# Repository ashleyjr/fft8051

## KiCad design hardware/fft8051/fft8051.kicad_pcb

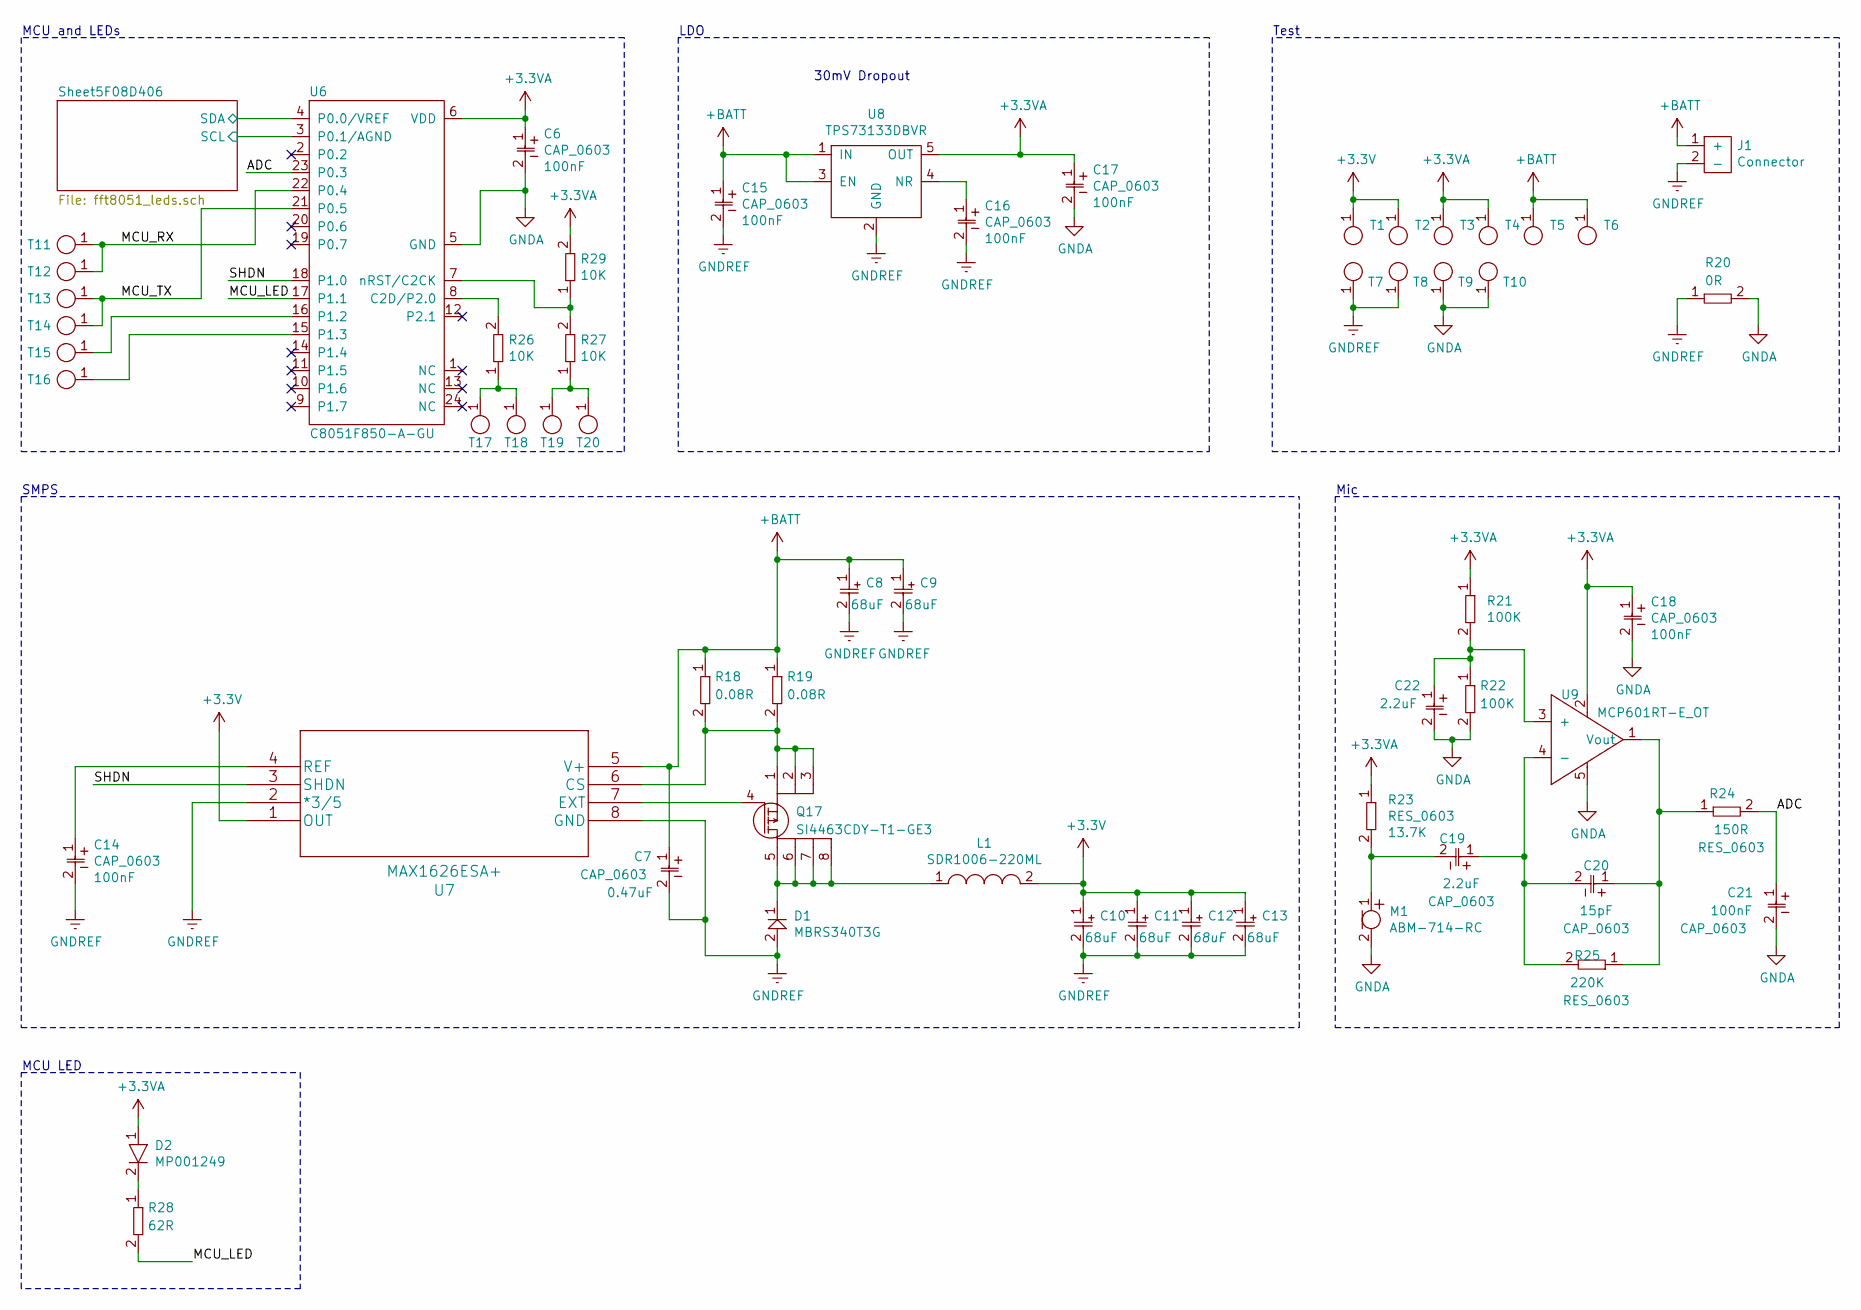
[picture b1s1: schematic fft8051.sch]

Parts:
C6, C7, C14, C15, C16, C17, C18, C19, C20, C21, C22: CAP_0603; 0603
C8, C9, C10, C11, C12, C13: T55B686M6R3C0070
D1: MBRS340T3G
D2: MP001249
J1: Connector
L1: SDR1006-220ML
M1: ABM-714-RC
Q17: SI4463CDY-T1-GE3
R18, R19, R20, R21, R22, R23, R24, R25, R26, R27, R28, R29: RES_0603; 0603
T1, T2, T3, T4, T5, T6, T7, T8, T9, T10, T11, T12, T13, T14, T15, T16, T17, T18, T19, T20: TestPoints; TestPoint
U6: C8051F850-A-GU
U7: MAX1626ESA+; MAX1626ESA&plus_
U8: TPS73133DBVR
U9: MCP601RT-E_OT; MCP601RT

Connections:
+3.3VA: C6.1, C17.1, C18.1, D2.1, R21.1, R23.1, R29.2, T3.1, T4.1, U6.6 (VDD), U8.5 (OUT), U9.2
+3V3: C10.1, C11.1, C12.1, C13.1, L1.2, T1.1, T2.1, U7.1 (OUT); also elsewhere on the board
+BATT: C7.1, C8.1, C9.1, C15.1, J1.1 (+), R18.1, R19.1, T5.1, T6.1, U7.5 (V+), U8.1 (IN), U8.3 (EN)
/ADC: C21.1, R24.2, U6.23 (P0.3)
/MCU_LED: R28.2, U6.17 (P1.1)
/MCU_RX: T11.1, T12.1, U6.22 (P0.4)
/MCU_TX: T13.1, T14.1, U6.21 (P0.5)
/SHDN: U6.18 (P1.0), U7.3 (SHDN)
/Sheet5F08D406/SCL: U6.3 (P0.1/AGND); also elsewhere on the board
/Sheet5F08D406/SDA: U6.4 (P0.0/VREF); also elsewhere on the board
GNDA: C6.2, C17.2, C18.2, C21.2, C22.2, M1.2, R20.2, R22.2, T9.1, T10.1, U6.5 (GND), U9.5
GNDREF: C7.2, C8.2, C9.2, C10.2, C11.2, C12.2, C13.2, C14.2, C15.2, C16.2, D1.2, J1.2 (-), R20.1, T7.1, T8.1, U7.2 (*3/5), U7.8 (GND), U8.2 (GND); also elsewhere on the board
unnamed: C14.1, U7.4 (REF)
unnamed: C16.1, U8.4 (NR)
unnamed: C19.1, C20.2, R25.2, U9.4 (-)
unnamed: C19.2, M1.1, R23.2
unnamed: C20.1, R24.1, R25.1, U9.1 (Vout)
unnamed: C22.1, R21.2, R22.1, U9.3 (+)
unnamed: D1.1, L1.1, Q17.5, Q17.6, Q17.7, Q17.8
unnamed: D2.2, R28.1
unnamed: Q17.1, Q17.2, Q17.3, R18.2, R19.2, U7.6 (CS)
unnamed: Q17.4, U7.7 (EXT)
unnamed: R26.1, T17.1, T18.1
unnamed: R26.2, U6.8 (C2D/P2.0)
unnamed: R27.1, T19.1, T20.1
unnamed: R27.2, R29.1, U6.7 (nRST/C2CK)
unnamed: T15.1, U6.16 (P1.2)
unnamed: T16.1, U6.15 (P1.3)

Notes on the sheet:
SMPS
MCU and LEDs
LDO
30mV Dropout
Test
Mic
MCU LED

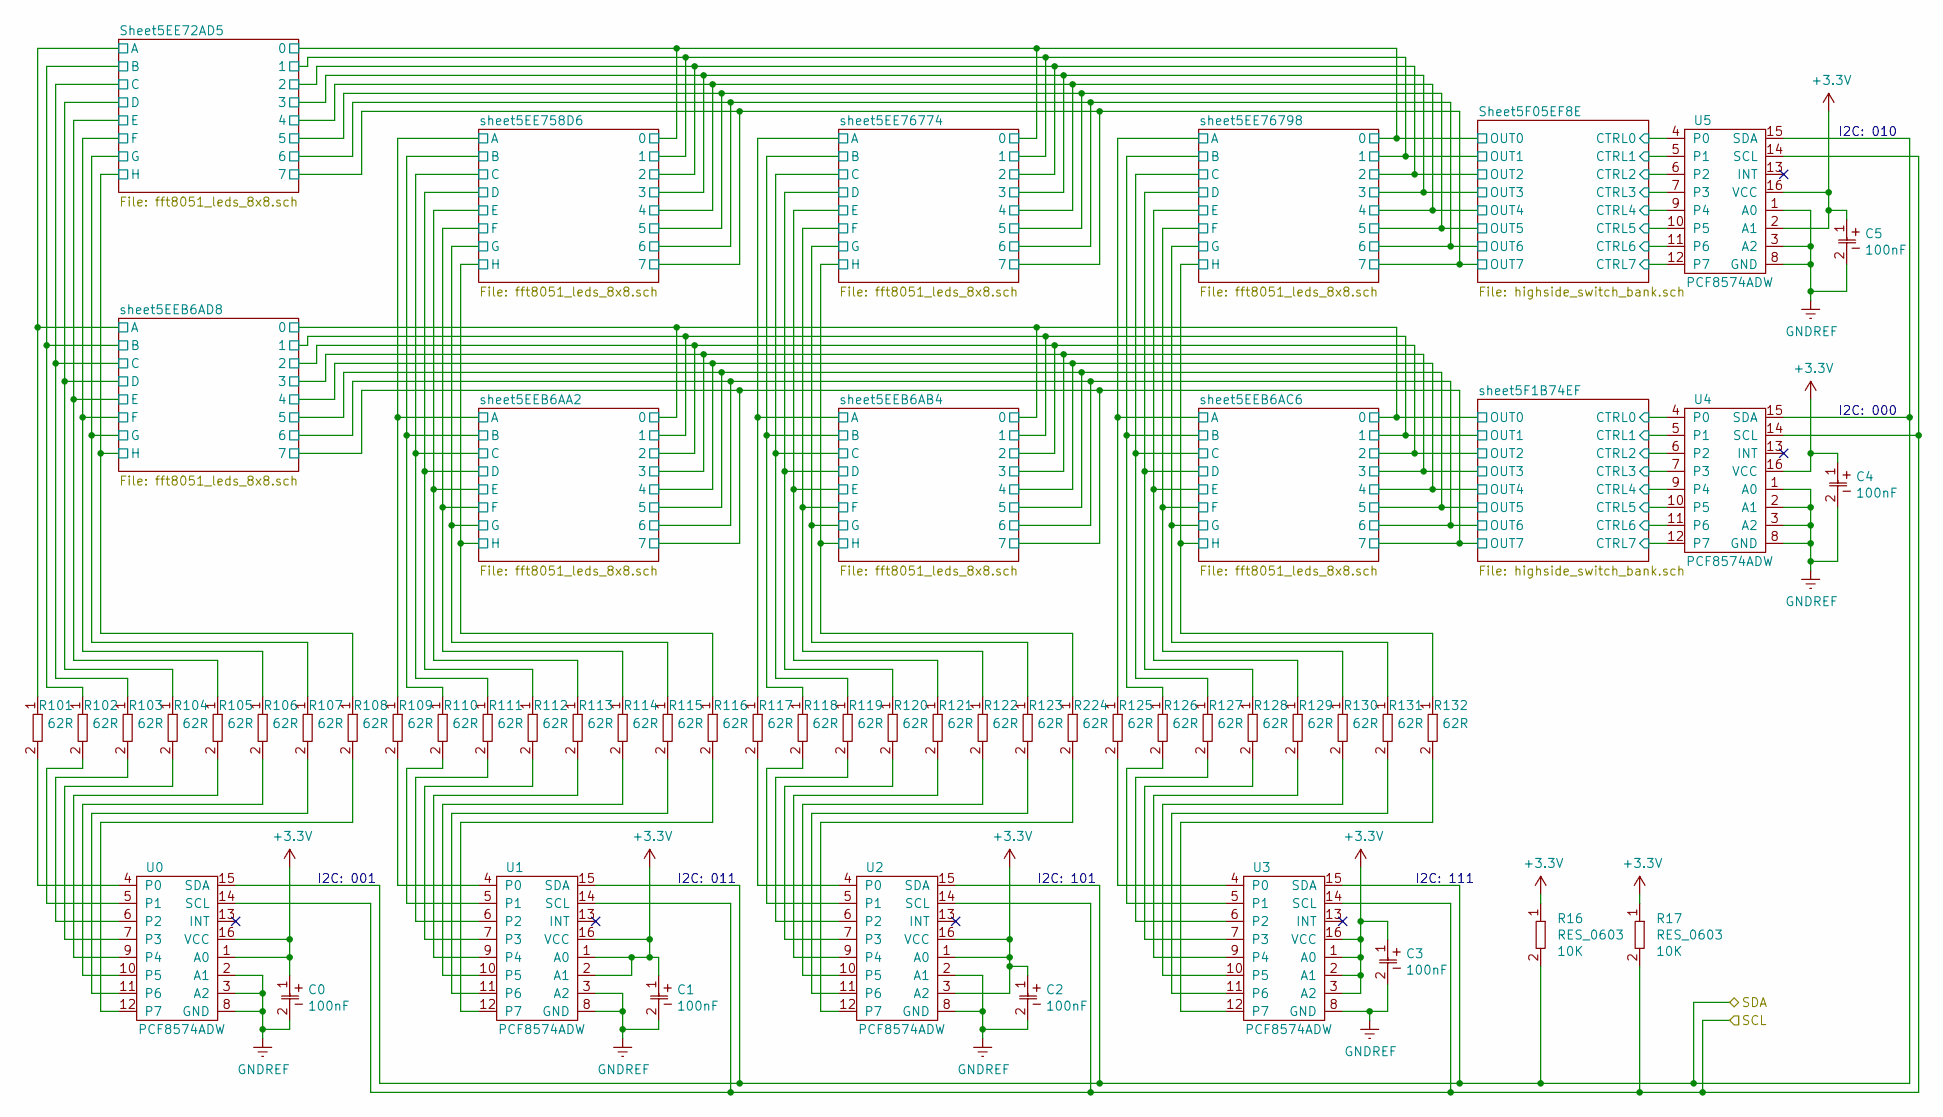
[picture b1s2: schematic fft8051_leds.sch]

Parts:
C0, C1, C2, C3, C4, C5: CAP_0603; 0603
R16, R17, R101, R102, R103, R104, R105, R106, R107, R108, R109, R110, R111, R112, R113, R114, R115, R116, R117, R118, R119, R120, R121, R122, R123, R125, R126, R127, R128, R129, R130, R131, R132, R224: RES_0603; 0603
U0, U1, U2, U3, U4, U5: PCF8574ADW

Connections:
+3V3: C0.1, C1.1, C2.1, C3.1, C4.1, C5.1, R16.1, R17.1, U0.1 (A0), U0.16 (VCC), U1.1 (A0), U1.2 (A1), U1.16 (VCC), U2.1 (A0), U2.3 (A2), U2.16 (VCC), U3.1 (A0), U3.2 (A1), U3.3 (A2), U3.16 (VCC), U4.16 (VCC), U5.2 (A1), U5.16 (VCC); also elsewhere on the board
/Sheet5F08D406/SCL: R17.2, U0.14 (SCL), U1.14 (SCL), U2.14 (SCL), U3.14 (SCL), U4.14 (SCL), U5.14 (SCL); also elsewhere on the board
/Sheet5F08D406/SDA: R16.2, U0.15 (SDA), U1.15 (SDA), U2.15 (SDA), U3.15 (SDA), U4.15 (SDA), U5.15 (SDA); also elsewhere on the board
/Sheet5F08D406/Sheet5EE72AD5/A: R101.1; also elsewhere on the board
/Sheet5F08D406/Sheet5EE72AD5/B: R102.1; also elsewhere on the board
/Sheet5F08D406/Sheet5EE72AD5/C: R103.1; also elsewhere on the board
/Sheet5F08D406/Sheet5EE72AD5/D: R104.1; also elsewhere on the board
/Sheet5F08D406/Sheet5EE72AD5/E: R105.1; also elsewhere on the board
/Sheet5F08D406/Sheet5EE72AD5/F: R106.1; also elsewhere on the board
/Sheet5F08D406/Sheet5EE72AD5/G: R107.1; also elsewhere on the board
/Sheet5F08D406/Sheet5EE72AD5/H: R108.1; also elsewhere on the board
/Sheet5F08D406/Sheet5F05EF8E/CTRL0: U5.4 (P0); also elsewhere on the board
/Sheet5F08D406/Sheet5F05EF8E/CTRL1: U5.5 (P1); also elsewhere on the board
/Sheet5F08D406/Sheet5F05EF8E/CTRL2: U5.6 (P2); also elsewhere on the board
/Sheet5F08D406/Sheet5F05EF8E/CTRL3: U5.7 (P3); also elsewhere on the board
/Sheet5F08D406/Sheet5F05EF8E/CTRL4: U5.9 (P4); also elsewhere on the board
/Sheet5F08D406/Sheet5F05EF8E/CTRL5: U5.10 (P5); also elsewhere on the board
/Sheet5F08D406/Sheet5F05EF8E/CTRL6: U5.11 (P6); also elsewhere on the board
/Sheet5F08D406/Sheet5F05EF8E/CTRL7: U5.12 (P7); also elsewhere on the board
/Sheet5F08D406/sheet5EE758D6/A: R109.1; also elsewhere on the board
/Sheet5F08D406/sheet5EE758D6/B: R110.1; also elsewhere on the board
/Sheet5F08D406/sheet5EE758D6/C: R111.1; also elsewhere on the board
/Sheet5F08D406/sheet5EE758D6/D: R112.1; also elsewhere on the board
/Sheet5F08D406/sheet5EE758D6/E: R113.1; also elsewhere on the board
/Sheet5F08D406/sheet5EE758D6/F: R114.1; also elsewhere on the board
/Sheet5F08D406/sheet5EE758D6/G: R115.1; also elsewhere on the board
/Sheet5F08D406/sheet5EE758D6/H: R116.1; also elsewhere on the board
/Sheet5F08D406/sheet5EE76774/A: R117.1; also elsewhere on the board
/Sheet5F08D406/sheet5EE76774/B: R118.1; also elsewhere on the board
/Sheet5F08D406/sheet5EE76774/C: R119.1; also elsewhere on the board
/Sheet5F08D406/sheet5EE76774/D: R120.1; also elsewhere on the board
/Sheet5F08D406/sheet5EE76774/E: R121.1; also elsewhere on the board
/Sheet5F08D406/sheet5EE76774/F: R122.1; also elsewhere on the board
/Sheet5F08D406/sheet5EE76774/G: R123.1; also elsewhere on the board
/Sheet5F08D406/sheet5EE76774/H: R224.1; also elsewhere on the board
/Sheet5F08D406/sheet5EE76798/A: R125.1; also elsewhere on the board
/Sheet5F08D406/sheet5EE76798/B: R126.1; also elsewhere on the board
/Sheet5F08D406/sheet5EE76798/C: R127.1; also elsewhere on the board
/Sheet5F08D406/sheet5EE76798/D: R128.1; also elsewhere on the board
/Sheet5F08D406/sheet5EE76798/E: R129.1; also elsewhere on the board
/Sheet5F08D406/sheet5EE76798/F: R130.1; also elsewhere on the board
/Sheet5F08D406/sheet5EE76798/G: R131.1; also elsewhere on the board
/Sheet5F08D406/sheet5EE76798/H: R132.1; also elsewhere on the board
/Sheet5F08D406/sheet5F1B74EF/CTRL0: U4.4 (P0); also elsewhere on the board
/Sheet5F08D406/sheet5F1B74EF/CTRL1: U4.5 (P1); also elsewhere on the board
/Sheet5F08D406/sheet5F1B74EF/CTRL2: U4.6 (P2); also elsewhere on the board
/Sheet5F08D406/sheet5F1B74EF/CTRL3: U4.7 (P3); also elsewhere on the board
/Sheet5F08D406/sheet5F1B74EF/CTRL4: U4.9 (P4); also elsewhere on the board
/Sheet5F08D406/sheet5F1B74EF/CTRL5: U4.10 (P5); also elsewhere on the board
/Sheet5F08D406/sheet5F1B74EF/CTRL6: U4.11 (P6); also elsewhere on the board
/Sheet5F08D406/sheet5F1B74EF/CTRL7: U4.12 (P7); also elsewhere on the board
GNDREF: C0.2, C1.2, C2.2, C3.2, C4.2, C5.2, U0.2 (A1), U0.3 (A2), U0.8 (GND), U1.3 (A2), U1.8 (GND), U2.2 (A1), U2.8 (GND), U3.8 (GND), U4.1 (A0), U4.2 (A1), U4.3 (A2), U4.8 (GND), U5.1 (A0), U5.3 (A2), U5.8 (GND); also elsewhere on the board
unnamed: R101.2, U0.4 (P0)
unnamed: R102.2, U0.5 (P1)
unnamed: R103.2, U0.6 (P2)
unnamed: R104.2, U0.7 (P3)
unnamed: R105.2, U0.9 (P4)
unnamed: R106.2, U0.10 (P5)
unnamed: R107.2, U0.11 (P6)
unnamed: R108.2, U0.12 (P7)
unnamed: R109.2, U1.4 (P0)
unnamed: R110.2, U1.5 (P1)
unnamed: R111.2, U1.6 (P2)
unnamed: R112.2, U1.7 (P3)
unnamed: R113.2, U1.9 (P4)
unnamed: R114.2, U1.10 (P5)
unnamed: R115.2, U1.11 (P6)
unnamed: R116.2, U1.12 (P7)
unnamed: R117.2, U2.4 (P0)
unnamed: R118.2, U2.5 (P1)
unnamed: R119.2, U2.6 (P2)
unnamed: R120.2, U2.7 (P3)
unnamed: R121.2, U2.9 (P4)
unnamed: R122.2, U2.10 (P5)
unnamed: R123.2, U2.11 (P6)
unnamed: R125.2, U3.4 (P0)
unnamed: R126.2, U3.5 (P1)
unnamed: R127.2, U3.6 (P2)
unnamed: R128.2, U3.7 (P3)
unnamed: R129.2, U3.9 (P4)
unnamed: R130.2, U3.10 (P5)
unnamed: R131.2, U3.11 (P6)
unnamed: R132.2, U3.12 (P7)
unnamed: R224.2, U2.12 (P7)

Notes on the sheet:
I2C: 111
I2C: 101
I2C: 011
I2C: 001
I2C: 000
I2C: 010

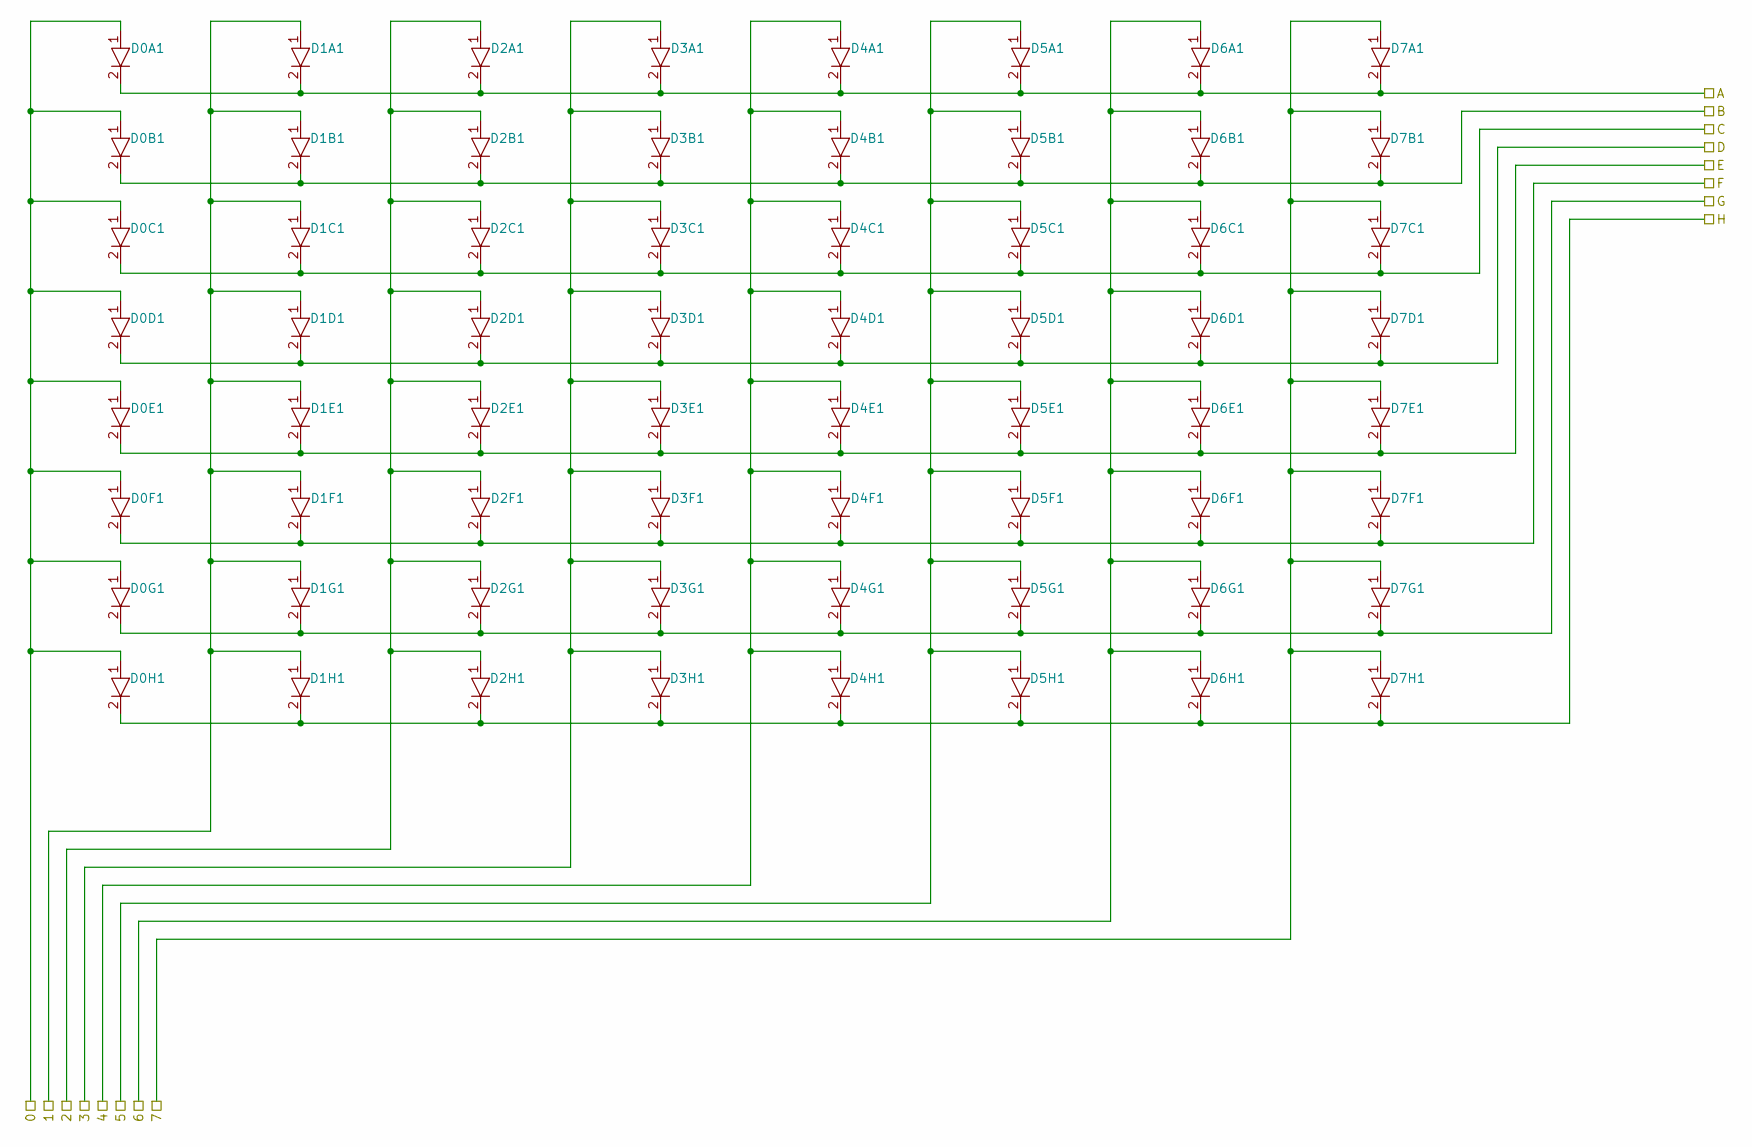
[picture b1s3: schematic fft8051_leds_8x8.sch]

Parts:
D0A1, D0B1, D0C1, D0D1, D0E1, D0F1, D0G1, D0H1, D1A1, D1B1, D1C1, D1D1, D1E1, D1F1, D1G1, D1H1, D2A1, D2B1, D2C1, D2D1, D2E1, D2F1, D2G1, D2H1, D3A1, D3B1, D3C1, D3D1, D3E1, D3F1, D3G1, D3H1, D4A1, D4B1, D4C1, D4D1, D4E1, D4F1, D4G1, D4H1, D5A1, D5B1, D5C1, D5D1, D5E1, D5F1, D5G1, D5H1, D6A1, D6B1, D6C1, D6D1, D6E1, D6F1, D6G1, D6H1, D7A1, D7B1, D7C1, D7D1, D7E1, D7F1, D7G1, D7H1: MP001249

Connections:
/Sheet5F08D406/Sheet5EE72AD5/0: D0A1.1, D0B1.1, D0C1.1, D0D1.1, D0E1.1, D0F1.1, D0G1.1, D0H1.1; also elsewhere on the board
/Sheet5F08D406/Sheet5EE72AD5/1: D1A1.1, D1B1.1, D1C1.1, D1D1.1, D1E1.1, D1F1.1, D1G1.1, D1H1.1; also elsewhere on the board
/Sheet5F08D406/Sheet5EE72AD5/2: D2A1.1, D2B1.1, D2C1.1, D2D1.1, D2E1.1, D2F1.1, D2G1.1, D2H1.1; also elsewhere on the board
/Sheet5F08D406/Sheet5EE72AD5/3: D3A1.1, D3B1.1, D3C1.1, D3D1.1, D3E1.1, D3F1.1, D3G1.1, D3H1.1; also elsewhere on the board
/Sheet5F08D406/Sheet5EE72AD5/4: D4A1.1, D4B1.1, D4C1.1, D4D1.1, D4E1.1, D4F1.1, D4G1.1, D4H1.1; also elsewhere on the board
/Sheet5F08D406/Sheet5EE72AD5/5: D5A1.1, D5B1.1, D5C1.1, D5D1.1, D5E1.1, D5F1.1, D5G1.1, D5H1.1; also elsewhere on the board
/Sheet5F08D406/Sheet5EE72AD5/6: D6A1.1, D6B1.1, D6C1.1, D6D1.1, D6E1.1, D6F1.1, D6G1.1, D6H1.1; also elsewhere on the board
/Sheet5F08D406/Sheet5EE72AD5/7: D7A1.1, D7B1.1, D7C1.1, D7D1.1, D7E1.1, D7F1.1, D7G1.1, D7H1.1; also elsewhere on the board
/Sheet5F08D406/sheet5EE758D6/A: D0A1.2, D1A1.2, D2A1.2, D3A1.2, D4A1.2, D5A1.2, D6A1.2, D7A1.2; also elsewhere on the board
/Sheet5F08D406/sheet5EE758D6/B: D0B1.2, D1B1.2, D2B1.2, D3B1.2, D4B1.2, D5B1.2, D6B1.2, D7B1.2; also elsewhere on the board
/Sheet5F08D406/sheet5EE758D6/C: D0C1.2, D1C1.2, D2C1.2, D3C1.2, D4C1.2, D5C1.2, D6C1.2, D7C1.2; also elsewhere on the board
/Sheet5F08D406/sheet5EE758D6/D: D0D1.2, D1D1.2, D2D1.2, D3D1.2, D4D1.2, D5D1.2, D6D1.2, D7D1.2; also elsewhere on the board
/Sheet5F08D406/sheet5EE758D6/E: D0E1.2, D1E1.2, D2E1.2, D3E1.2, D4E1.2, D5E1.2, D6E1.2, D7E1.2; also elsewhere on the board
/Sheet5F08D406/sheet5EE758D6/F: D0F1.2, D1F1.2, D2F1.2, D3F1.2, D4F1.2, D5F1.2, D6F1.2, D7F1.2; also elsewhere on the board
/Sheet5F08D406/sheet5EE758D6/G: D0G1.2, D1G1.2, D2G1.2, D3G1.2, D4G1.2, D5G1.2, D6G1.2, D7G1.2; also elsewhere on the board
/Sheet5F08D406/sheet5EE758D6/H: D0H1.2, D1H1.2, D2H1.2, D3H1.2, D4H1.2, D5H1.2, D6H1.2, D7H1.2; also elsewhere on the board

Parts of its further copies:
D0A2, D0A3, D0A4, D0A5, D0A6, D0A7, D0A8, D0B2, D0B3, D0B4, D0B5, D0B6, D0B7, D0B8, D0C2, D0C3, D0C4, D0C5, D0C6, D0C7, D0C8, D0D2, D0D3, D0D4, D0D5, D0D6, D0D7, D0D8, D0E2, D0E3, D0E4, D0E5, D0E6, D0E7, D0E8, D0F2, D0F3, D0F4, D0F5, D0F6, D0F7, D0F8, D0G2, D0G3, D0G4, D0G5, D0G6, D0G7, D0G8, D0H2, D0H3, D0H4, D0H5, D0H6, D0H7, D0H8, D1A2, D1A3, D1A4, D1A5, D1A6, D1A7, D1A8, D1B2, D1B3, D1B4, D1B5, D1B6, D1B7, D1B8, D1C2, D1C3, D1C4, D1C5, D1C6, D1C7, D1C8, D1D2, D1D3, D1D4, D1D5, D1D6, D1D7, D1D8, D1E2, D1E3, D1E4, D1E5, D1E6, D1E7, D1E8, D1F2, D1F3, D1F4, D1F5, D1F6, D1F7, D1F8, D1G2, D1G3, D1G4, D1G5, D1G6, D1G7, D1G8, D1H2, D1H3, D1H4, D1H5, D1H6, D1H7, D1H8, D2A2, D2A3, D2A4, D2A5, D2A6, D2A7, D2A8, D2B2, D2B3, D2B4, D2B5, D2B6, D2B7, D2B8, D2C2, D2C3, D2C4, D2C5, D2C6, D2C7, D2C8, D2D2, D2D3, D2D4, D2D5, D2D6, D2D7, D2D8, D2E2, D2E3, D2E4, D2E5, D2E6, D2E7, D2E8, D2F2, D2F3, D2F4, D2F5, D2F6, D2F7, D2F8, D2G2, D2G3, D2G4, D2G5, D2G6, D2G7, D2G8, D2H2, D2H3, D2H4, D2H5, D2H6, D2H7, D2H8, D3A2, D3A3, D3A4, D3A5, D3A6, D3A7, D3A8, D3B2, D3B3, D3B4, D3B5, D3B6, D3B7, D3B8, D3C2, D3C3, D3C4, D3C5, D3C6, D3C7, D3C8, D3D2, D3D3, D3D4, D3D5, D3D6, D3D7, D3D8, D3E2, D3E3, D3E4, D3E5, D3E6, D3E7, D3E8, D3F2, D3F3, D3F4, D3F5, D3F6, D3F7, D3F8, D3G2, D3G3, D3G4, D3G5, D3G6, D3G7, D3G8, D3H2, D3H3, D3H4, D3H5, D3H6, D3H7, D3H8, D4A2, D4A3, D4A4, D4A5, D4A6, D4A7, D4A8, D4B2, D4B3, D4B4, D4B5, D4B6, D4B7, D4B8, D4C2, D4C3, D4C4, D4C5, D4C6, D4C7, D4C8, D4D2, D4D3, D4D4, D4D5, D4D6, D4D7, D4D8, D4E2, D4E3, D4E4, D4E5, D4E6, D4E7, D4E8, D4F2, D4F3, D4F4, D4F5, D4F6, D4F7, D4F8, D4G2, D4G3, D4G4, D4G5, D4G6, D4G7, D4G8, D4H2, D4H3, D4H4, D4H5, D4H6, D4H7, D4H8, D5A2, D5A3, D5A4, D5A5, D5A6, D5A7, D5A8, D5B2, D5B3, D5B4, D5B5, D5B6, D5B7, D5B8, D5C2, D5C3, D5C4, D5C5, D5C6, D5C7, D5C8, D5D2, D5D3, D5D4, D5D5, D5D6, D5D7, D5D8, D5E2, D5E3, D5E4, D5E5, D5E6, D5E7, D5E8, D5F2, D5F3, D5F4, D5F5, D5F6, D5F7, D5F8, D5G2, D5G3, D5G4, D5G5, D5G6, D5G7, D5G8, D5H2, D5H3, D5H4, D5H5, D5H6, D5H7, D5H8, D6A2, D6A3, D6A4, D6A5, D6A6, D6A7, D6A8, D6B2, D6B3, D6B4, D6B5, D6B6, D6B7, D6B8, D6C2, D6C3, D6C4, D6C5, D6C6, D6C7, D6C8, D6D2, D6D3, D6D4, D6D5, D6D6, D6D7, D6D8, D6E2, D6E3, D6E4, D6E5, D6E6, D6E7, D6E8, D6F2, D6F3, D6F4, D6F5, D6F6, D6F7, D6F8, D6G2, D6G3, D6G4, D6G5, D6G6, D6G7, D6G8, D6H2, D6H3, D6H4, D6H5, D6H6, D6H7, D6H8, D7A2, D7A3, D7A4, D7A5, D7A6, D7A7, D7A8, D7B2, D7B3, D7B4, D7B5, D7B6, D7B7, D7B8, D7C2, D7C3, D7C4, D7C5, D7C6, D7C7, D7C8, D7D2, D7D3, D7D4, D7D5, D7D6, D7D7, D7D8, D7E2, D7E3, D7E4, D7E5, D7E6, D7E7, D7E8, D7F2, D7F3, D7F4, D7F5, D7F6, D7F7, D7F8, D7G2, D7G3, D7G4, D7G5, D7G6, D7G7, D7G8, D7H2, D7H3, D7H4, D7H5, D7H6, D7H7, D7H8: MP001249

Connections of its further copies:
/Sheet5F08D406/Sheet5EE72AD5/0: D0A2.1, D0A3.1, D0A4.1, D0B2.1, D0B3.1, D0B4.1, D0C2.1, D0C3.1, D0C4.1, D0D2.1, D0D3.1, D0D4.1, D0E2.1, D0E3.1, D0E4.1, D0F2.1, D0F3.1, D0F4.1, D0G2.1, D0G3.1, D0G4.1, D0H2.1, D0H3.1, D0H4.1; also elsewhere on the board
/Sheet5F08D406/Sheet5EE72AD5/1: D1A2.1, D1A3.1, D1A4.1, D1B2.1, D1B3.1, D1B4.1, D1C2.1, D1C3.1, D1C4.1, D1D2.1, D1D3.1, D1D4.1, D1E2.1, D1E3.1, D1E4.1, D1F2.1, D1F3.1, D1F4.1, D1G2.1, D1G3.1, D1G4.1, D1H2.1, D1H3.1, D1H4.1; also elsewhere on the board
/Sheet5F08D406/Sheet5EE72AD5/2: D2A2.1, D2A3.1, D2A4.1, D2B2.1, D2B3.1, D2B4.1, D2C2.1, D2C3.1, D2C4.1, D2D2.1, D2D3.1, D2D4.1, D2E2.1, D2E3.1, D2E4.1, D2F2.1, D2F3.1, D2F4.1, D2G2.1, D2G3.1, D2G4.1, D2H2.1, D2H3.1, D2H4.1; also elsewhere on the board
/Sheet5F08D406/Sheet5EE72AD5/3: D3A2.1, D3A3.1, D3A4.1, D3B2.1, D3B3.1, D3B4.1, D3C2.1, D3C3.1, D3C4.1, D3D2.1, D3D3.1, D3D4.1, D3E2.1, D3E3.1, D3E4.1, D3F2.1, D3F3.1, D3F4.1, D3G2.1, D3G3.1, D3G4.1, D3H2.1, D3H3.1, D3H4.1; also elsewhere on the board
/Sheet5F08D406/Sheet5EE72AD5/4: D4A2.1, D4A3.1, D4A4.1, D4B2.1, D4B3.1, D4B4.1, D4C2.1, D4C3.1, D4C4.1, D4D2.1, D4D3.1, D4D4.1, D4E2.1, D4E3.1, D4E4.1, D4F2.1, D4F3.1, D4F4.1, D4G2.1, D4G3.1, D4G4.1, D4H2.1, D4H3.1, D4H4.1; also elsewhere on the board
/Sheet5F08D406/Sheet5EE72AD5/5: D5A2.1, D5A3.1, D5A4.1, D5B2.1, D5B3.1, D5B4.1, D5C2.1, D5C3.1, D5C4.1, D5D2.1, D5D3.1, D5D4.1, D5E2.1, D5E3.1, D5E4.1, D5F2.1, D5F3.1, D5F4.1, D5G2.1, D5G3.1, D5G4.1, D5H2.1, D5H3.1, D5H4.1; also elsewhere on the board
/Sheet5F08D406/Sheet5EE72AD5/6: D6A2.1, D6A3.1, D6A4.1, D6B2.1, D6B3.1, D6B4.1, D6C2.1, D6C3.1, D6C4.1, D6D2.1, D6D3.1, D6D4.1, D6E2.1, D6E3.1, D6E4.1, D6F2.1, D6F3.1, D6F4.1, D6G2.1, D6G3.1, D6G4.1, D6H2.1, D6H3.1, D6H4.1; also elsewhere on the board
/Sheet5F08D406/Sheet5EE72AD5/7: D7A2.1, D7A3.1, D7A4.1, D7B2.1, D7B3.1, D7B4.1, D7C2.1, D7C3.1, D7C4.1, D7D2.1, D7D3.1, D7D4.1, D7E2.1, D7E3.1, D7E4.1, D7F2.1, D7F3.1, D7F4.1, D7G2.1, D7G3.1, D7G4.1, D7H2.1, D7H3.1, D7H4.1; also elsewhere on the board
/Sheet5F08D406/Sheet5EE72AD5/A: D0A4.2, D0A8.2, D1A4.2, D1A8.2, D2A4.2, D2A8.2, D3A4.2, D3A8.2, D4A4.2, D4A8.2, D5A4.2, D5A8.2, D6A4.2, D6A8.2, D7A4.2, D7A8.2; also elsewhere on the board
/Sheet5F08D406/Sheet5EE72AD5/B: D0B4.2, D0B8.2, D1B4.2, D1B8.2, D2B4.2, D2B8.2, D3B4.2, D3B8.2, D4B4.2, D4B8.2, D5B4.2, D5B8.2, D6B4.2, D6B8.2, D7B4.2, D7B8.2; also elsewhere on the board
/Sheet5F08D406/Sheet5EE72AD5/C: D0C4.2, D0C8.2, D1C4.2, D1C8.2, D2C4.2, D2C8.2, D3C4.2, D3C8.2, D4C4.2, D4C8.2, D5C4.2, D5C8.2, D6C4.2, D6C8.2, D7C4.2, D7C8.2; also elsewhere on the board
/Sheet5F08D406/Sheet5EE72AD5/D: D0D4.2, D0D8.2, D1D4.2, D1D8.2, D2D4.2, D2D8.2, D3D4.2, D3D8.2, D4D4.2, D4D8.2, D5D4.2, D5D8.2, D6D4.2, D6D8.2, D7D4.2, D7D8.2; also elsewhere on the board
/Sheet5F08D406/Sheet5EE72AD5/E: D0E4.2, D0E8.2, D1E4.2, D1E8.2, D2E4.2, D2E8.2, D3E4.2, D3E8.2, D4E4.2, D4E8.2, D5E4.2, D5E8.2, D6E4.2, D6E8.2, D7E4.2, D7E8.2; also elsewhere on the board
/Sheet5F08D406/Sheet5EE72AD5/F: D0F4.2, D0F8.2, D1F4.2, D1F8.2, D2F4.2, D2F8.2, D3F4.2, D3F8.2, D4F4.2, D4F8.2, D5F4.2, D5F8.2, D6F4.2, D6F8.2, D7F4.2, D7F8.2; also elsewhere on the board
/Sheet5F08D406/Sheet5EE72AD5/G: D0G4.2, D0G8.2, D1G4.2, D1G8.2, D2G4.2, D2G8.2, D3G4.2, D3G8.2, D4G4.2, D4G8.2, D5G4.2, D5G8.2, D6G4.2, D6G8.2, D7G4.2, D7G8.2; also elsewhere on the board
/Sheet5F08D406/Sheet5EE72AD5/H: D0H4.2, D0H8.2, D1H4.2, D1H8.2, D2H4.2, D2H8.2, D3H4.2, D3H8.2, D4H4.2, D4H8.2, D5H4.2, D5H8.2, D6H4.2, D6H8.2, D7H4.2, D7H8.2; also elsewhere on the board
/Sheet5F08D406/sheet5EE758D6/A: D0A5.2, D1A5.2, D2A5.2, D3A5.2, D4A5.2, D5A5.2, D6A5.2, D7A5.2; also elsewhere on the board
/Sheet5F08D406/sheet5EE758D6/B: D0B5.2, D1B5.2, D2B5.2, D3B5.2, D4B5.2, D5B5.2, D6B5.2, D7B5.2; also elsewhere on the board
/Sheet5F08D406/sheet5EE758D6/C: D0C5.2, D1C5.2, D2C5.2, D3C5.2, D4C5.2, D5C5.2, D6C5.2, D7C5.2; also elsewhere on the board
/Sheet5F08D406/sheet5EE758D6/D: D0D5.2, D1D5.2, D2D5.2, D3D5.2, D4D5.2, D5D5.2, D6D5.2, D7D5.2; also elsewhere on the board
/Sheet5F08D406/sheet5EE758D6/E: D0E5.2, D1E5.2, D2E5.2, D3E5.2, D4E5.2, D5E5.2, D6E5.2, D7E5.2; also elsewhere on the board
/Sheet5F08D406/sheet5EE758D6/F: D0F5.2, D1F5.2, D2F5.2, D3F5.2, D4F5.2, D5F5.2, D6F5.2, D7F5.2; also elsewhere on the board
/Sheet5F08D406/sheet5EE758D6/G: D0G5.2, D1G5.2, D2G5.2, D3G5.2, D4G5.2, D5G5.2, D6G5.2, D7G5.2; also elsewhere on the board
/Sheet5F08D406/sheet5EE758D6/H: D0H5.2, D1H5.2, D2H5.2, D3H5.2, D4H5.2, D5H5.2, D6H5.2, D7H5.2; also elsewhere on the board
/Sheet5F08D406/sheet5EE76774/A: D0A2.2, D0A6.2, D1A2.2, D1A6.2, D2A2.2, D2A6.2, D3A2.2, D3A6.2, D4A2.2, D4A6.2, D5A2.2, D5A6.2, D6A2.2, D6A6.2, D7A2.2, D7A6.2; also elsewhere on the board
/Sheet5F08D406/sheet5EE76774/B: D0B2.2, D0B6.2, D1B2.2, D1B6.2, D2B2.2, D2B6.2, D3B2.2, D3B6.2, D4B2.2, D4B6.2, D5B2.2, D5B6.2, D6B2.2, D6B6.2, D7B2.2, D7B6.2; also elsewhere on the board
/Sheet5F08D406/sheet5EE76774/C: D0C2.2, D0C6.2, D1C2.2, D1C6.2, D2C2.2, D2C6.2, D3C2.2, D3C6.2, D4C2.2, D4C6.2, D5C2.2, D5C6.2, D6C2.2, D6C6.2, D7C2.2, D7C6.2; also elsewhere on the board
/Sheet5F08D406/sheet5EE76774/D: D0D2.2, D0D6.2, D1D2.2, D1D6.2, D2D2.2, D2D6.2, D3D2.2, D3D6.2, D4D2.2, D4D6.2, D5D2.2, D5D6.2, D6D2.2, D6D6.2, D7D2.2, D7D6.2; also elsewhere on the board
/Sheet5F08D406/sheet5EE76774/E: D0E2.2, D0E6.2, D1E2.2, D1E6.2, D2E2.2, D2E6.2, D3E2.2, D3E6.2, D4E2.2, D4E6.2, D5E2.2, D5E6.2, D6E2.2, D6E6.2, D7E2.2, D7E6.2; also elsewhere on the board
/Sheet5F08D406/sheet5EE76774/F: D0F2.2, D0F6.2, D1F2.2, D1F6.2, D2F2.2, D2F6.2, D3F2.2, D3F6.2, D4F2.2, D4F6.2, D5F2.2, D5F6.2, D6F2.2, D6F6.2, D7F2.2, D7F6.2; also elsewhere on the board
/Sheet5F08D406/sheet5EE76774/G: D0G2.2, D0G6.2, D1G2.2, D1G6.2, D2G2.2, D2G6.2, D3G2.2, D3G6.2, D4G2.2, D4G6.2, D5G2.2, D5G6.2, D6G2.2, D6G6.2, D7G2.2, D7G6.2; also elsewhere on the board
/Sheet5F08D406/sheet5EE76774/H: D0H2.2, D0H6.2, D1H2.2, D1H6.2, D2H2.2, D2H6.2, D3H2.2, D3H6.2, D4H2.2, D4H6.2, D5H2.2, D5H6.2, D6H2.2, D6H6.2, D7H2.2, D7H6.2; also elsewhere on the board
/Sheet5F08D406/sheet5EE76798/A: D0A3.2, D0A7.2, D1A3.2, D1A7.2, D2A3.2, D2A7.2, D3A3.2, D3A7.2, D4A3.2, D4A7.2, D5A3.2, D6A3.2, D6A7.2, D7A3.2, D7A7.2; also elsewhere on the board
/Sheet5F08D406/sheet5EE76798/B: D0B3.2, D0B7.2, D1B3.2, D1B7.2, D2B3.2, D2B7.2, D3B3.2, D3B7.2, D4B3.2, D4B7.2, D5B3.2, D5B7.2, D6B3.2, D6B7.2, D7B3.2, D7B7.2; also elsewhere on the board
/Sheet5F08D406/sheet5EE76798/C: D0C3.2, D0C7.2, D1C3.2, D1C7.2, D2C3.2, D2C7.2, D3C3.2, D3C7.2, D4C3.2, D4C7.2, D5C3.2, D5C7.2, D6C3.2, D6C7.2, D7C3.2, D7C7.2; also elsewhere on the board
/Sheet5F08D406/sheet5EE76798/D: D0D3.2, D0D7.2, D1D3.2, D1D7.2, D2D3.2, D2D7.2, D3D3.2, D3D7.2, D4D3.2, D4D7.2, D5D3.2, D5D7.2, D6D3.2, D6D7.2, D7D3.2, D7D7.2; also elsewhere on the board
/Sheet5F08D406/sheet5EE76798/E: D0E3.2, D0E7.2, D1E3.2, D1E7.2, D2E3.2, D2E7.2, D3E3.2, D3E7.2, D4E3.2, D4E7.2, D5E3.2, D5E7.2, D6E3.2, D6E7.2, D7E3.2, D7E7.2; also elsewhere on the board
/Sheet5F08D406/sheet5EE76798/F: D0F3.2, D0F7.2, D1F3.2, D1F7.2, D2F3.2, D2F7.2, D3F3.2, D3F7.2, D4F3.2, D4F7.2, D5F3.2, D5F7.2, D6F3.2, D6F7.2, D7F3.2, D7F7.2; also elsewhere on the board
/Sheet5F08D406/sheet5EE76798/G: D0G3.2, D0G7.2, D1G3.2, D1G7.2, D2G3.2, D2G7.2, D3G3.2, D3G7.2, D4G3.2, D4G7.2, D5G3.2, D5G7.2, D6G3.2, D6G7.2, D7G3.2, D7G7.2; also elsewhere on the board
/Sheet5F08D406/sheet5EE76798/H: D0H3.2, D0H7.2, D1H3.2, D1H7.2, D2H3.2, D2H7.2, D3H3.2, D3H7.2, D4H3.2, D4H7.2, D5H3.2, D5H7.2, D6H3.2, D6H7.2, D7H3.2, D7H7.2; also elsewhere on the board
/Sheet5F08D406/sheet5EEB6AA2/0: D0A5.1, D0A6.1, D0A7.1, D0A8.1, D0B5.1, D0B6.1, D0B7.1, D0B8.1, D0C5.1, D0C6.1, D0C7.1, D0C8.1, D0D5.1, D0D6.1, D0D7.1, D0D8.1, D0E5.1, D0E6.1, D0E7.1, D0E8.1, D0F5.1, D0F6.1, D0F7.1, D0F8.1, D0G5.1, D0G6.1, D0G7.1, D0G8.1, D0H5.1, D0H6.1, D0H7.1, D0H8.1; also elsewhere on the board
/Sheet5F08D406/sheet5EEB6AA2/1: D1A5.1, D1A6.1, D1A7.1, D1A8.1, D1B5.1, D1B6.1, D1B7.1, D1B8.1, D1C5.1, D1C6.1, D1C7.1, D1C8.1, D1D5.1, D1D6.1, D1D7.1, D1D8.1, D1E5.1, D1E6.1, D1E7.1, D1E8.1, D1F5.1, D1F6.1, D1F7.1, D1F8.1, D1G5.1, D1G6.1, D1G7.1, D1G8.1, D1H5.1, D1H6.1, D1H7.1, D1H8.1; also elsewhere on the board
/Sheet5F08D406/sheet5EEB6AA2/2: D2A5.1, D2A6.1, D2A7.1, D2A8.1, D2B5.1, D2B6.1, D2B7.1, D2B8.1, D2C5.1, D2C6.1, D2C7.1, D2C8.1, D2D5.1, D2D6.1, D2D7.1, D2D8.1, D2E5.1, D2E6.1, D2E7.1, D2E8.1, D2F5.1, D2F6.1, D2F7.1, D2F8.1, D2G5.1, D2G6.1, D2G7.1, D2G8.1, D2H5.1, D2H6.1, D2H7.1, D2H8.1; also elsewhere on the board
/Sheet5F08D406/sheet5EEB6AA2/3: D3A5.1, D3A6.1, D3A7.1, D3A8.1, D3B5.1, D3B6.1, D3B7.1, D3B8.1, D3C5.1, D3C6.1, D3C7.1, D3C8.1, D3D5.1, D3D6.1, D3D7.1, D3D8.1, D3E5.1, D3E6.1, D3E7.1, D3E8.1, D3F5.1, D3F6.1, D3F7.1, D3F8.1, D3G5.1, D3G6.1, D3G7.1, D3G8.1, D3H5.1, D3H6.1, D3H7.1, D3H8.1; also elsewhere on the board
/Sheet5F08D406/sheet5EEB6AA2/4: D4A5.1, D4A6.1, D4A7.1, D4A8.1, D4B5.1, D4B6.1, D4B7.1, D4B8.1, D4C5.1, D4C6.1, D4C7.1, D4C8.1, D4D5.1, D4D6.1, D4D7.1, D4D8.1, D4E5.1, D4E6.1, D4E7.1, D4E8.1, D4F5.1, D4F6.1, D4F7.1, D4F8.1, D4G5.1, D4G6.1, D4G7.1, D4G8.1, D4H5.1, D4H6.1, D4H7.1, D4H8.1; also elsewhere on the board
/Sheet5F08D406/sheet5EEB6AA2/5: D5A5.1, D5A6.1, D5A8.1, D5B5.1, D5B6.1, D5B7.1, D5B8.1, D5C5.1, D5C6.1, D5C7.1, D5C8.1, D5D5.1, D5D6.1, D5D7.1, D5D8.1, D5E5.1, D5E6.1, D5E7.1, D5E8.1, D5F5.1, D5F6.1, D5F7.1, D5F8.1, D5G5.1, D5G6.1, D5G7.1, D5G8.1, D5H5.1, D5H6.1, D5H7.1, D5H8.1; also elsewhere on the board
/Sheet5F08D406/sheet5EEB6AA2/6: D6A5.1, D6A6.1, D6A7.1, D6A8.1, D6B5.1, D6B6.1, D6B7.1, D6B8.1, D6C5.1, D6C6.1, D6C7.1, D6C8.1, D6D5.1, D6D6.1, D6D7.1, D6D8.1, D6E5.1, D6E6.1, D6E7.1, D6E8.1, D6F5.1, D6F6.1, D6F7.1, D6F8.1, D6G5.1, D6G6.1, D6G7.1, D6G8.1, D6H5.1, D6H6.1, D6H7.1, D6H8.1; also elsewhere on the board
/Sheet5F08D406/sheet5EEB6AA2/7: D7A5.1, D7A6.1, D7A7.1, D7A8.1, D7B5.1, D7B6.1, D7B7.1, D7B8.1, D7C5.1, D7C6.1, D7C7.1, D7C8.1, D7D5.1, D7D6.1, D7D7.1, D7D8.1, D7E5.1, D7E6.1, D7E7.1, D7E8.1, D7F5.1, D7F6.1, D7F7.1, D7F8.1, D7G5.1, D7G6.1, D7G7.1, D7G8.1, D7H5.1, D7H6.1, D7H7.1, D7H8.1; also elsewhere on the board

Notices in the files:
parts and their libraries:
Copyright 2016 Accelerated Designs. All rights reserved.
